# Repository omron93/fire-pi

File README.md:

FireFighter robot - Hledat a hasit 
==================================
Robot for national competition of RoboRave in Czech Republic called: Amavet 

National: http://amavet.cz/

International: http://roboquerque.org/

Robot description:
==================
Block-scheme.png is best for imagination how it works.

In short:
=========
WebCam + Raspberry Pi looking for candle. If Candle is see. Raspberry send information about position to STM32F4 over USART.

STM32F4 is main procesor with main program.

This robot wins first place in Czech republic in year 2013! But team from second place, flew to New Mexico and wins first place in International competition and defeated the home teams!

Final try from Mexico: http://www.youtube.com/watch?v=NQRlYmdfuB4

http://roboquerque.org/global-outreach/czech-republic/

If you use this project, specialy for this competition. Tell me about it, please, and I maybe help you. :)
==========================================================================================================

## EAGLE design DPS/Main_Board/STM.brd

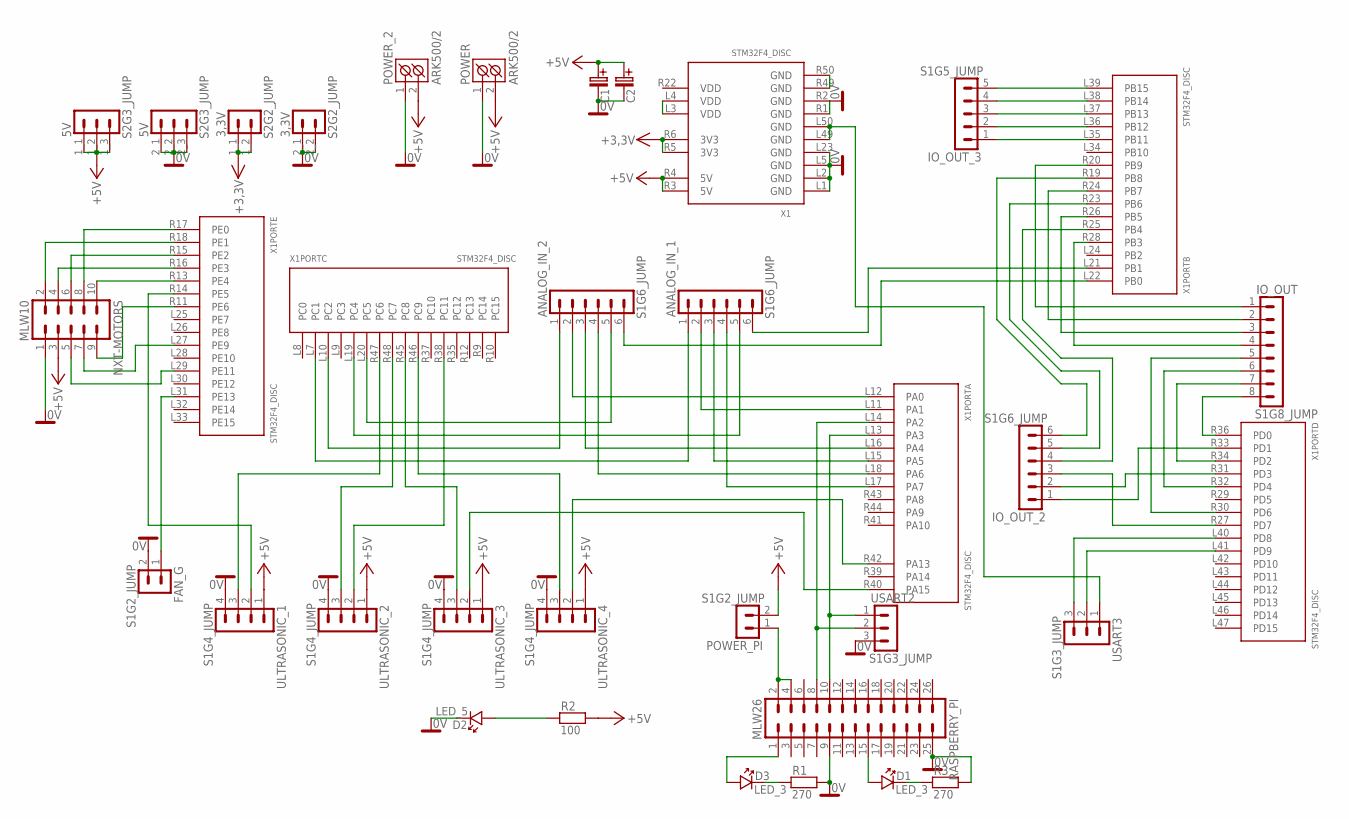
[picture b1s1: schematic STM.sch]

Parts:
3,3V: S2G2_JUMP; S2G2_JUM
5V: S2G3_JUMP; S2G3_JUM
ANALOG_IN_1, ANALOG_IN_2: S1G6_JUMP; S1G6_JUM
C1, C2: #_RADIAL_POUZDRA5; C_EL_5
D1, D3: LED_3
D2: LED_5
FAN_G: S1G2_JUMP; S1G2_JUM
IO_OUT: S1G8_JUMP; S1G8_JUM
IO_OUT_2: S1G6_JUMP; S1G6_JUM
IO_OUT_3: S1G5_JUMP; S1G5_JUM
NXT-MOTORS: MLW10; MLW10G
POWER: ARK500/2
POWER_2: ARK500/2
POWER_PI: S1G2_JUMP; S1G2_JUM
R1, R3: 270; R_7,5
R2: 100; R_7,5
RASPBERRY_PI: MLW26; MLW26G
ULTRASONIC_1, ULTRASONIC_2, ULTRASONIC_3, ULTRASONIC_4: S1G4_JUMP; S1G4_JUM
USART2, USART3: S1G3_JUMP; S1G3_JUM
X1: STM32F4_DISC

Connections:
0V: 3,3V.2_1 (1), 3,3V.2_2 (2), 5V.2_1 (1), 5V.2_2 (2), 5V.2_3 (3), C1.C- (C_EL-), C2.C- (C_EL-), D2.K, FAN_G.2, NXT-MOTORS.1, POWER.1 (K1), POWER_2.1 (K1), R1.2, R3.2, RASPBERRY_PI.9, RASPBERRY_PI.25, ULTRASONIC_1.4, ULTRASONIC_2.4, ULTRASONIC_3.4, ULTRASONIC_4.4, USART2.3, X1.L1 (GND), X1.L2 (GND), X1.L5 (GND), X1.L23 (GND), X1.R1 (GND), X1.R2 (GND)
+5V: 5V.1_1 (1), 5V.1_2 (2), 5V.1_3 (3), C1.C+ (C_EL+), C2.C+ (C_EL+), NXT-MOTORS.3, POWER.2 (K2), POWER_2.2 (K2), POWER_PI.2, R2.2, ULTRASONIC_1.1, ULTRASONIC_2.1, ULTRASONIC_3.1, ULTRASONIC_4.1, X1.R3 (5V), X1.R4 (5V)
unnamed: ANALOG_IN_1.6, X1.L21 (PB1)
unnamed: NXT-MOTORS.8, X1.R17 (PE0)
unnamed: RASPBERRY_PI.8, USART2.2, X1.L14 (PA2)
unnamed: RASPBERRY_PI.10, USART2.1, X1.L13 (PA3)
unnamed: USART3.2, X1.L41 (PD9)
unnamed: USART3.3, X1.L40 (PD8)
unnamed: NXT-MOTORS.2, X1.R18 (PE1)
unnamed: NXT-MOTORS.6, X1.R15 (PE2)
unnamed: NXT-MOTORS.10, X1.R13 (PE4)
unnamed: NXT-MOTORS.4, X1.R16 (PE3)
unnamed: NXT-MOTORS.5, X1.L29 (PE11)
unnamed: ULTRASONIC_1.2, X1.R14 (PE5)
unnamed: NXT-MOTORS.7, X1.L27 (PE9)
unnamed: NXT-MOTORS.9, X1.R11 (PE6)
unnamed: ULTRASONIC_1.3, X1.R47 (PC6)
unnamed: ULTRASONIC_4.3, X1.R46 (PC9)
unnamed: ULTRASONIC_2.3, X1.R48 (PC7)
unnamed: ULTRASONIC_3.3, X1.R45 (PC8)
unnamed: ANALOG_IN_2.3, X1.L16 (PA4)
unnamed: ANALOG_IN_1.2, X1.L11 (PA1)
unnamed: ANALOG_IN_2.2, X1.L12 (PA0)
unnamed: ANALOG_IN_1.3, X1.L15 (PA5)
unnamed: ANALOG_IN_1.4, X1.L17 (PA7)
unnamed: ANALOG_IN_2.4, X1.L18 (PA6)
unnamed: ANALOG_IN_2.6, X1.L22 (PB0)
unnamed: X1.L3 (VDD), X1.L4 (VDD)
unnamed: FAN_G.1, X1.L31 (PE13)
unnamed: D1.K, R3.1
unnamed: D1.A, RASPBERRY_PI.15
unnamed: D2.A, R2.1
unnamed: IO_OUT.4, X1.R28 (PB3)
unnamed: IO_OUT.3, X1.R26 (PB5)
unnamed: IO_OUT.2, X1.R24 (PB7)
unnamed: IO_OUT_2.3, X1.R27 (PD7)
unnamed: IO_OUT.5, X1.R30 (PD6)
unnamed: IO_OUT.6, X1.R32 (PD4)
unnamed: IO_OUT_2.2, X1.R31 (PD3)
unnamed: IO_OUT.7, X1.R34 (PD2)
unnamed: IO_OUT_2.1, X1.R33 (PD1)
unnamed: IO_OUT.8, X1.R36 (PD0)
unnamed: IO_OUT.1, X1.R20 (PB9)
unnamed: IO_OUT_2.5, X1.R23 (PB6)
unnamed: IO_OUT_3.2, X1.L36 (PB12)
unnamed: D3.K, R1.1
unnamed: IO_OUT_3.4, X1.L38 (PB14)
unnamed: IO_OUT_2.6, X1.R19 (PB8)
unnamed: IO_OUT_2.4, X1.R25 (PB4)
unnamed: IO_OUT_3.1, X1.L35 (PB11)
unnamed: D3.A, RASPBERRY_PI.1
unnamed: IO_OUT_3.3, X1.L37 (PB13)
unnamed: POWER_PI.1, RASPBERRY_PI.2, RASPBERRY_PI.4
unnamed: IO_OUT_3.5, X1.L39 (PB15)
unnamed: USART3.1, X1.L49 (GND), X1.L50 (GND)
unnamed: ANALOG_IN_2.5, X1.L20 (PC5)
unnamed: ANALOG_IN_1.5, X1.L19 (PC4)
unnamed: ANALOG_IN_2.1, X1.L10 (PC2)
unnamed: ANALOG_IN_1.1, X1.L7 (PC1)
unnamed: ULTRASONIC_2.2, X1.R38 (PC11)
unnamed: ULTRASONIC_3.2, X1.R40 (PA15)
unnamed: ULTRASONIC_4.2, X1.R42 (PA13)
unnamed: X1.R49 (GND), X1.R50 (GND)
VCC: 3,3V.1_1 (1), 3,3V.1_2 (2), X1.R5 (3V3), X1.R6 (3V3)
VDD: X1.R22 (VDD)

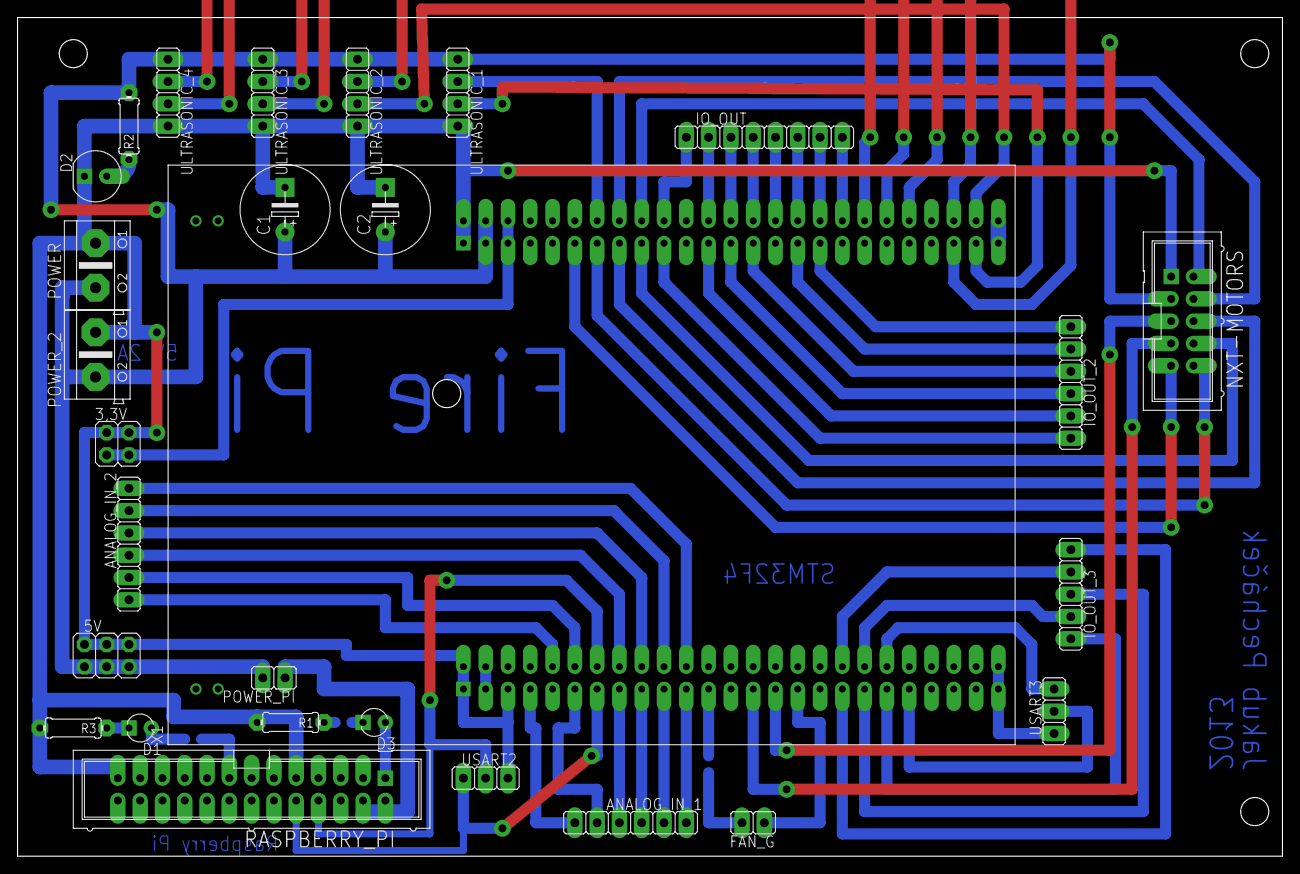
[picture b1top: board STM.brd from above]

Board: 2 copper layers, 144.1 x 95.6 mm, 28 parts (0 on the bottom side), 64 nets.

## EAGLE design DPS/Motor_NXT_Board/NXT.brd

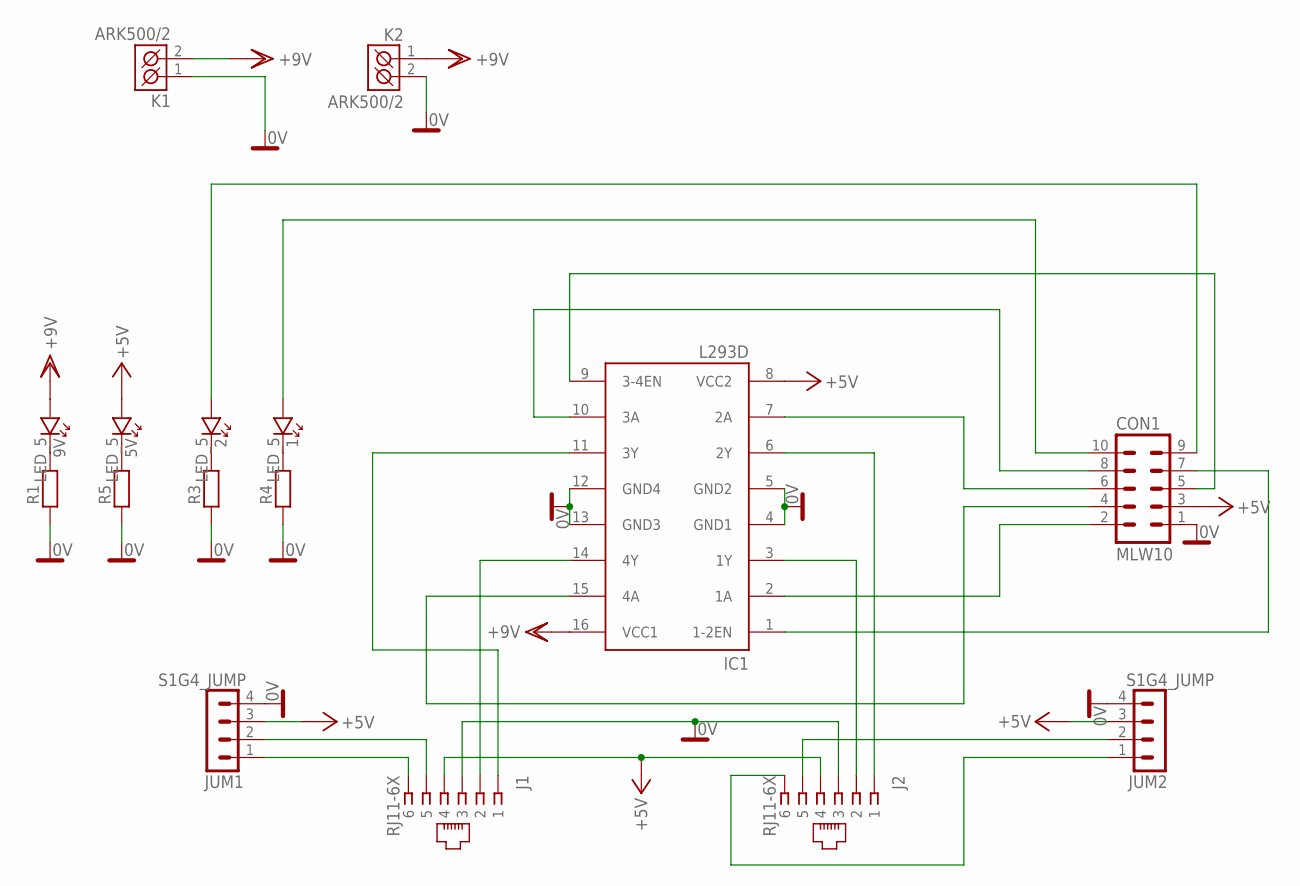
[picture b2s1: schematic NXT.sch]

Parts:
1, 2, 5V, 9V: LED_5
CON1: MLW10; MLW10G
IC1: L293D; DIL16
J1, J2: RJ11-6X; RJ11-NO_SHIELD
JUM1, JUM2: S1G4_JUMP; S1G4_JUM
K1, K2: ARK500/2
R1, R3, R4, R5: R_10; R-10

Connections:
0V: CON1.1, IC1.4 (GND1), IC1.5 (GND2), IC1.12 (GND4), IC1.13 (GND3), J1.3, J2.3, JUM1.4, JUM2.4, K1.1 (K1), K2.2 (K2), R1.1, R3.1, R4.1, R5.1
+5V: 5V.A, CON1.3, IC1.8 (VCC2), J1.4, J2.4, JUM1.3, JUM2.3
+9V: 9V.A, IC1.16 (VCC1), K1.2 (K2), K2.1 (K1)
unnamed: IC1.11 (3Y), J1.1
unnamed: IC1.14 (4Y), J1.2
unnamed: CON1.6, IC1.7 (2A)
unnamed: CON1.2, IC1.2 (1A)
unnamed: IC1.3 (1Y), J2.2
unnamed: IC1.6 (2Y), J2.1
unnamed: CON1.7, IC1.1 (1-2EN)
unnamed: CON1.5, IC1.9 (3-4EN)
unnamed: CON1.8, IC1.10 (3A)
unnamed: CON1.4, IC1.15 (4A)
unnamed: 1.A, CON1.10
unnamed: 2.A, CON1.9
unnamed: 9V.K, R1.2
unnamed: 5V.K, R5.2
unnamed: 2.K, R3.2
unnamed: 1.K, R4.2
unnamed: J2.5, JUM2.2
unnamed: J2.6, JUM2.1
unnamed: J1.5, JUM1.2
unnamed: J1.6, JUM1.1

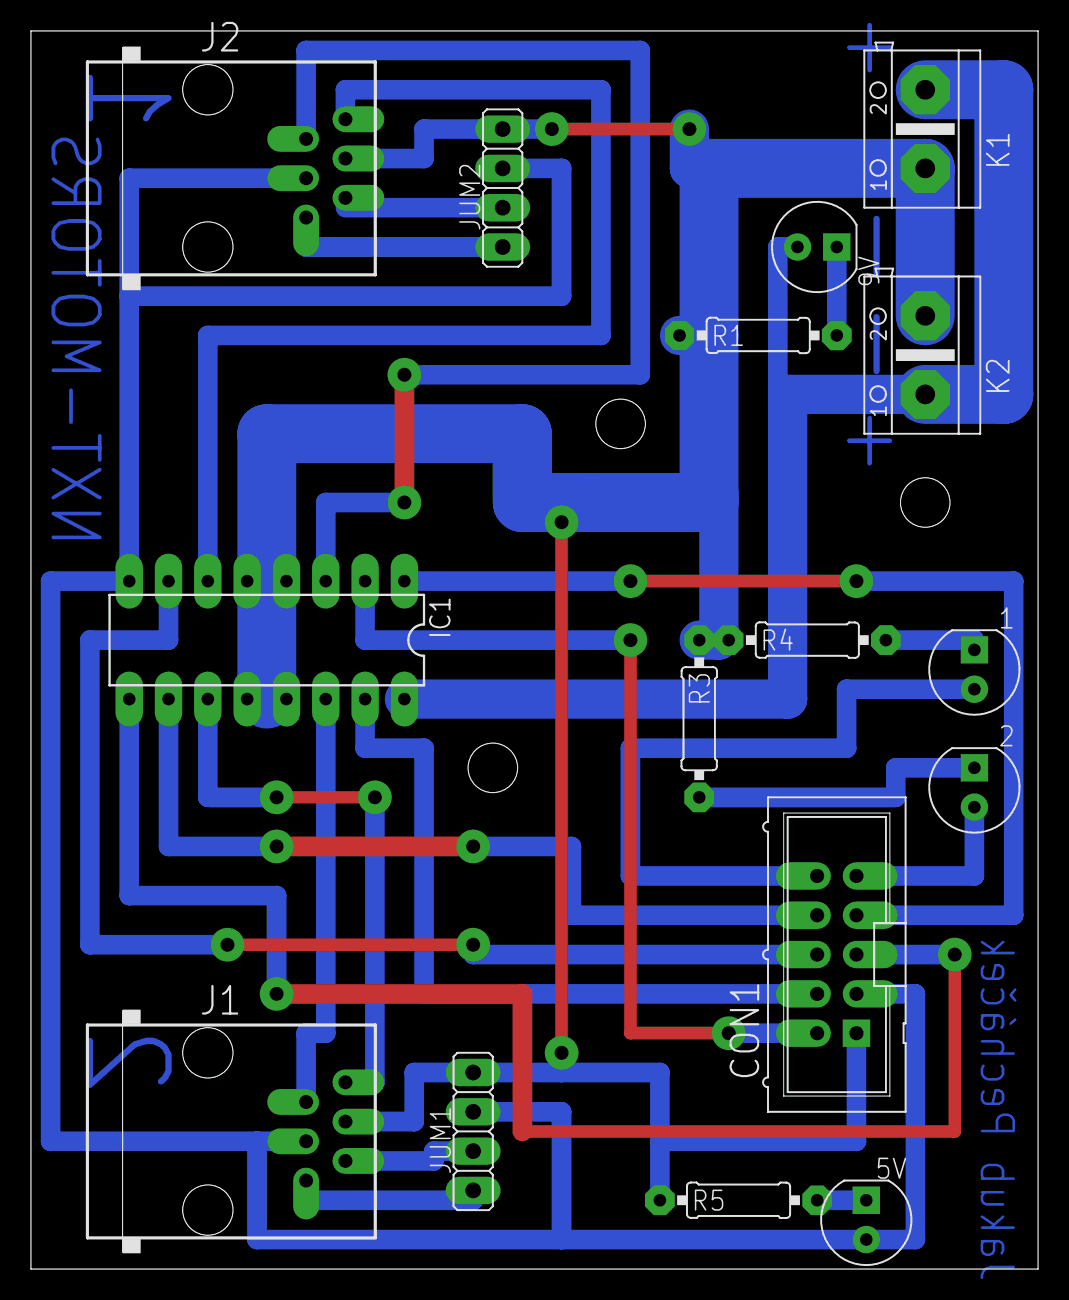
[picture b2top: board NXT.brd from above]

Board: 2 copper layers, 65.1 x 80.0 mm, 16 parts (0 on the bottom side), 23 nets.

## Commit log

2013-03-05 Initial commit.
2013-03-05 uprava
2013-03-05 Added README file.
2013-03-05 testt
2013-03-07 encodery
2013-03-07 Raspberry Pi - Soft
2013-03-09 cara funguje
2013-03-09 Project reorganization - use make (Makefile) instead of IDE compiling.
2013-03-09 Ultrazvuk+encodery
2013-03-11 ADC funguje
2013-03-13 ADC + IR -> OK
2013-03-15 raspi - gui switch
2013-03-15 New candle detection - cca 3m
2013-03-16 Added GCC-like compiler + Makefile.
2013-03-16 First Candle Blow
2013-03-17 Block + length move
2013-03-17 Problem with float
2013-03-18 Candle find - parametres
2013-03-18 template matching
2013-03-19 Programs access
2013-03-19 Templ func ++
2013-03-20 Programs for find Candle
2013-03-21 Added more programs
2013-03-21 Go_to_center
2013-03-27 Final program for competition
2013-04-03 added menu + wall program
2014-01-21 Project reorganization + README added
2014-01-21 DPS + Documentation added
2014-08-03 New program for candle detection -> 'Candle detector'

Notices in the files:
parts and their libraries:
Copyright (C) PaJa 2011
Copyright (C) PaJa 2001-2011
Copyright (C) PaJa 2003-2009
